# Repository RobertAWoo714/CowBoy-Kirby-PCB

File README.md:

# Cowboy Gradcap PCBs

This was just a graduation gift for me and my girlfriend for our undergrad. I made this 2 hours :p

Made in KiCAD 9

Features:
* 16 white SMD LED
* 3.0V coin cell battery

## Pictures

<div style="text-align: center;">
  
</div>

<div style="text-align: center;">
    
</div>

<div style="text-align: center;">
    
</div>

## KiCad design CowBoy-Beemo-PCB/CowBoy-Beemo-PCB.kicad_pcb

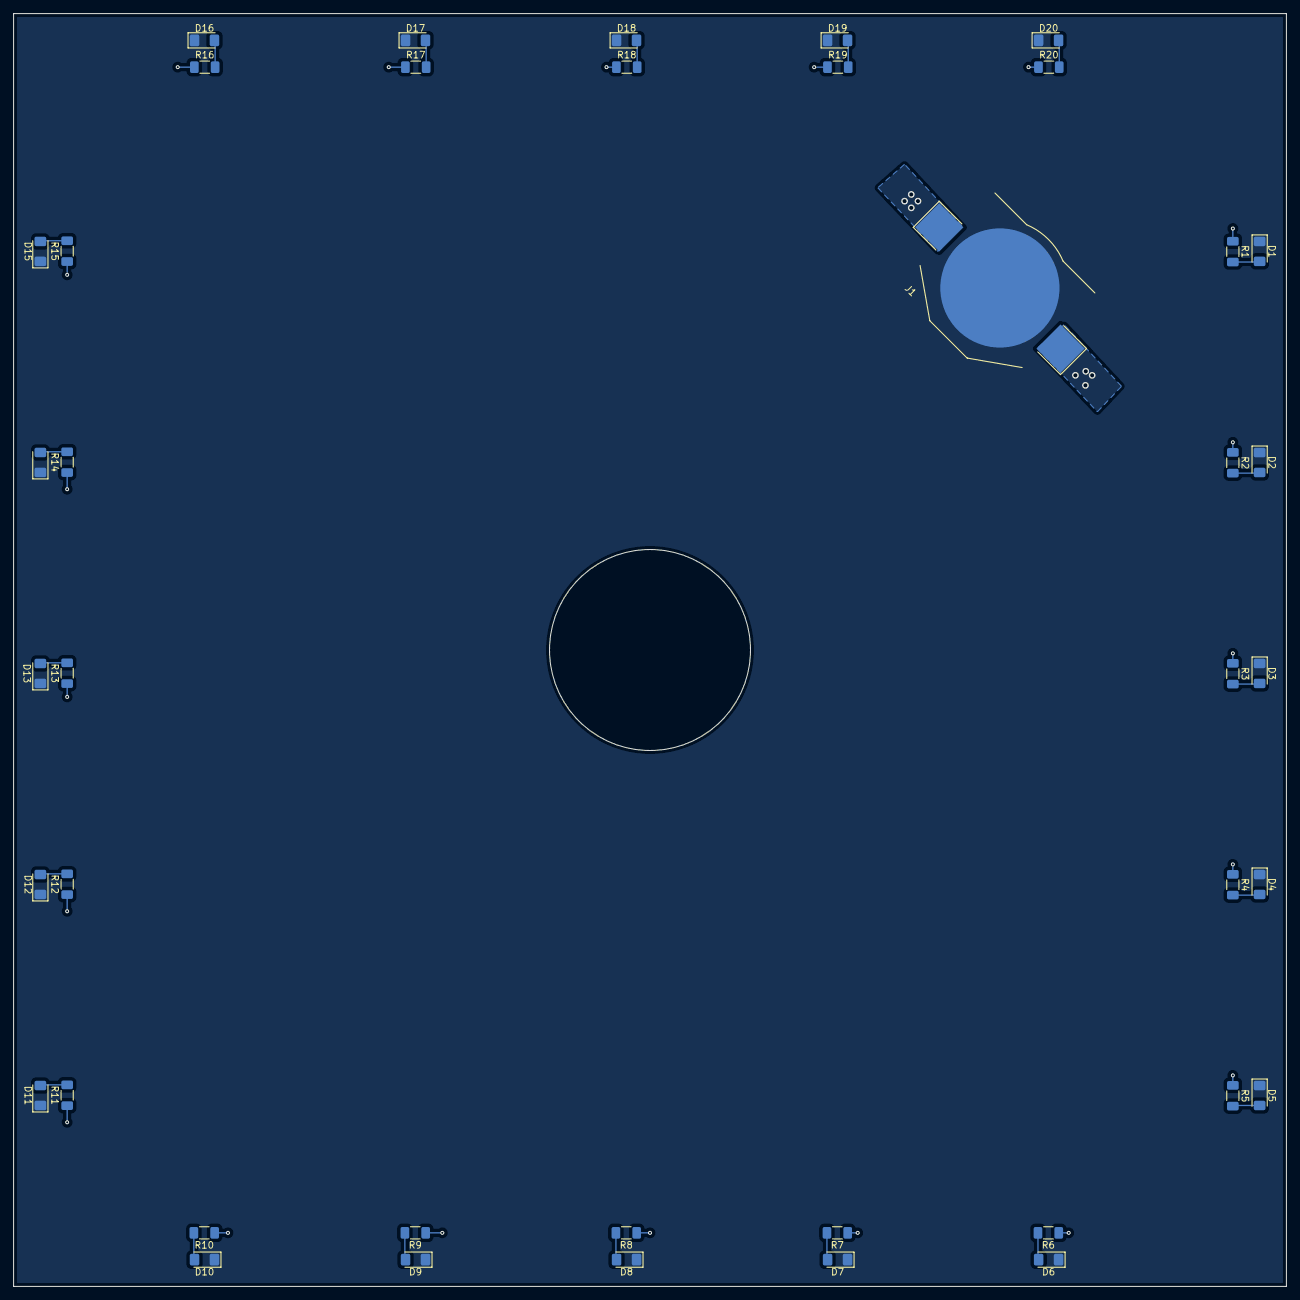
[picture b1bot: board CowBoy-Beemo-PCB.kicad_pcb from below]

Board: 2 copper layers, 190.0 x 190.0 mm, 41 parts (41 on the bottom side), 22 nets.

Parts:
D1, D2, D3, D4, D5, D6, D7, D8, D9, D10, D11, D12, D13, D14, D15, D16, D17, D18, D19, D20: LED; LED_1206_3216Metric_Pad1.42x1.75mm_HandSolder
J1: Conn_01x02_Pin; BatteryHolder_Keystone_3002_1x2032
R1, R2, R3, R4, R5, R6, R7, R8, R9, R10, R11, R12, R13, R14, R15, R16, R17, R18, R19, R20: 20Ω; R_1206_3216Metric_Pad1.30x1.75mm_HandSolder

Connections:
GND: D1.1 (K), D2.1 (K), D3.1 (K), D4.1 (K), D5.1 (K), D6.1 (K), D7.1 (K), D8.1 (K), D9.1 (K), D10.1 (K), D11.1 (K), D12.1 (K), D13.1 (K), D14.1 (K), D15.1 (K), D16.1 (K), D17.1 (K), D18.1 (K), D19.1 (K), D20.1 (K), J1.2
unnamed: D1.2 (A), R1.2
unnamed: D2.2 (A), R2.2
unnamed: D3.2 (A), R3.2
unnamed: D4.2 (A), R4.2
unnamed: D5.2 (A), R5.2
unnamed: D6.2 (A), R6.2
unnamed: D7.2 (A), R7.2
unnamed: D8.2 (A), R8.2
unnamed: D9.2 (A), R9.2
unnamed: D10.2 (A), R10.2
unnamed: D11.2 (A), R11.2
unnamed: D12.2 (A), R12.2
unnamed: D13.2 (A), R13.2
unnamed: D14.2 (A), R14.2
unnamed: D15.2 (A), R15.2
unnamed: D16.2 (A), R16.2
unnamed: D17.2 (A), R17.2
unnamed: D18.2 (A), R18.2
unnamed: D19.2 (A), R19.2
unnamed: D20.2 (A), R20.2
VBUS: J1.1, R1.1, R2.1, R3.1, R4.1, R5.1, R6.1, R7.1, R8.1, R9.1, R10.1, R11.1, R12.1, R13.1, R14.1, R15.1, R16.1, R17.1, R18.1, R19.1, R20.1

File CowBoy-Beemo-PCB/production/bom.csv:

Designator,Footprint,Quantity,Value,LCSC Part #
"D1, D10, D11, D12, D13, D14, D15, D16, D17, D18, D19, D2, D20, D3, D4, D5, D6, D7, D8, D9",1206,20,LED,
J1,BatteryHolder_Keystone_3002_1x2032,1,Conn_01x02_Pin,
"R1, R10, R11, R12, R13, R14, R15, R16, R17, R18, R19, R2, R20, R3, R4, R5, R6, R7, R8, R9",1206,20,20Ω,

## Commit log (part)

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2026-05-31 Done
